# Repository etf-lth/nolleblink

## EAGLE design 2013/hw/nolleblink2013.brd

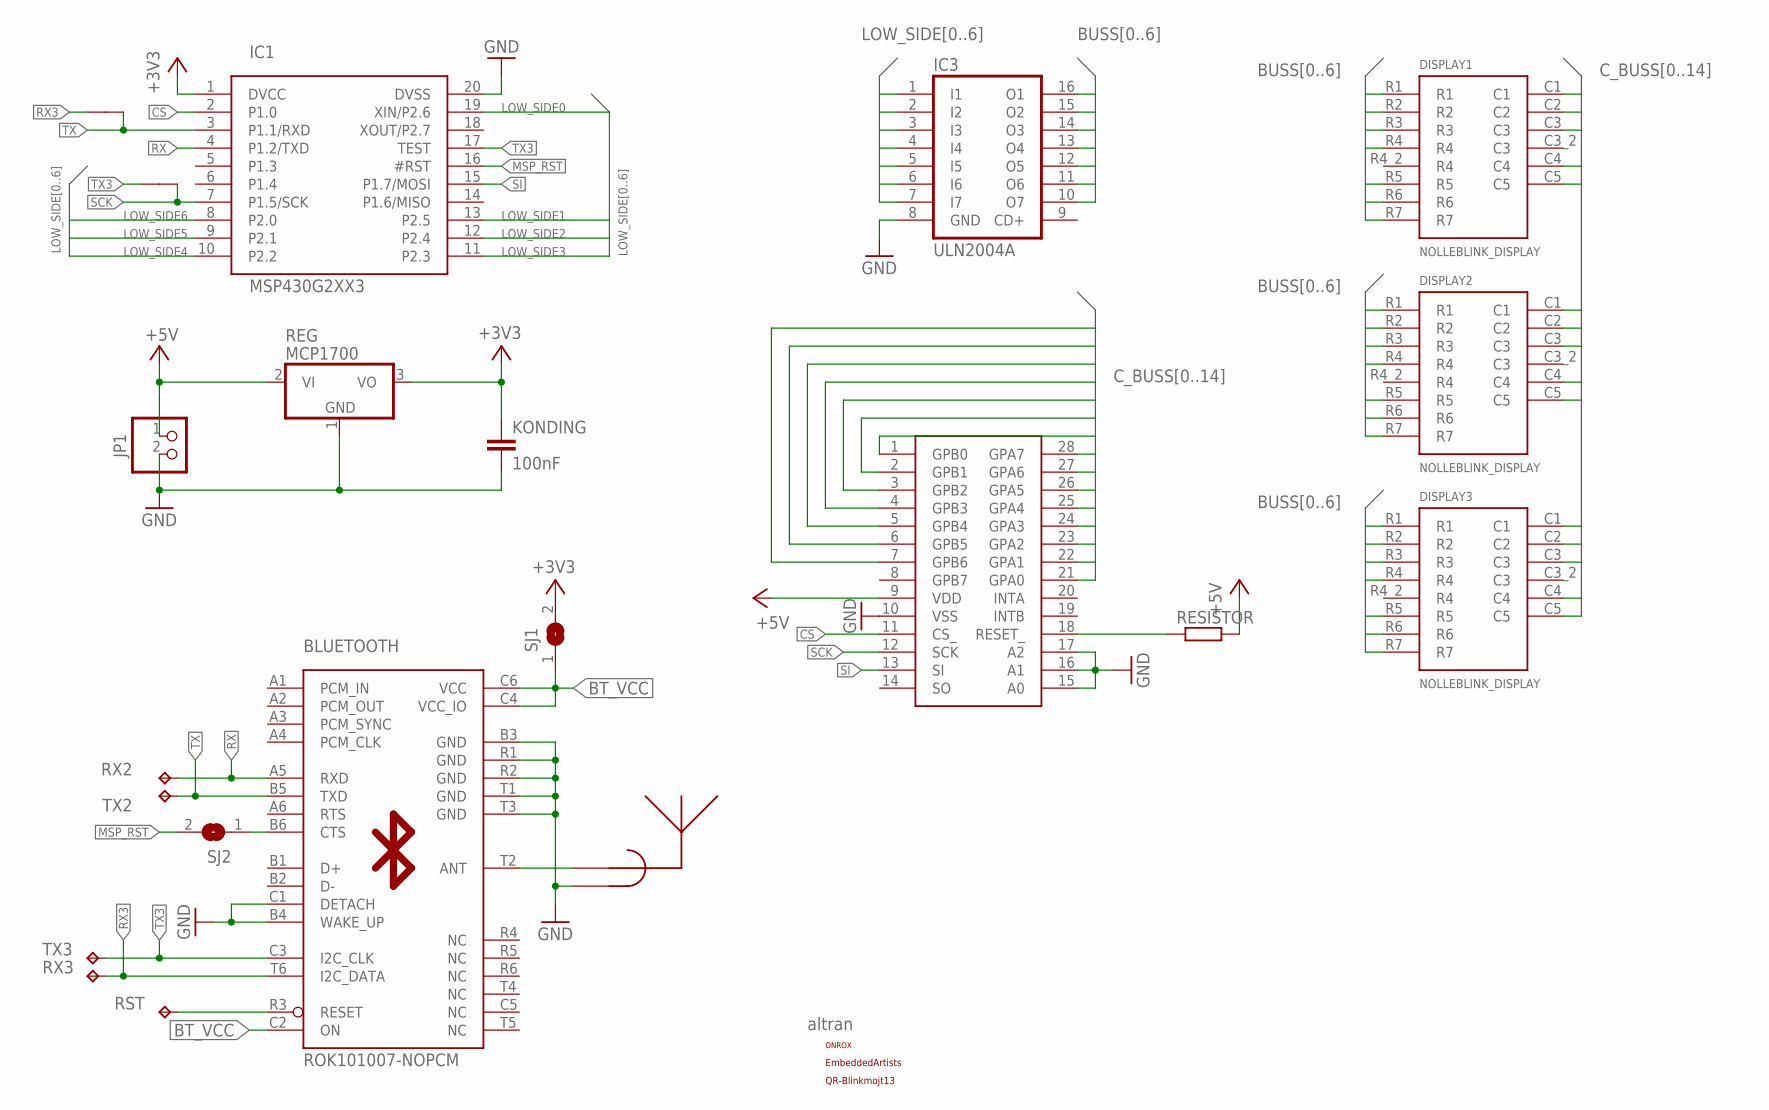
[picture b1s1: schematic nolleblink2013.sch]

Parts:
BLUETOOTH: ROK101007-NOPCM; ROK101007_NOPCM
DISPLAY1, DISPLAY2, DISPLAY3: NOLLEBLINK_DISPLAY; KINGBRIGHT_TA12-11EWA
IC1: MSP430G2XX3; N20
IC2: MCPS23S17; MCP23S17
IC3: ULN2004A; DIL16
JP1: PINHD-1X2; 1X02
KONDING: 100nF; C050-030X075
REG: MCP1700; TO92_REGULATOR
RESISTOR: R-EU_0207/10; 0207/10
RST: TPTP12SQ; TP12SQ
RX2: TPTP20SQ; TP20SQ
RX3: TPTP12SQ; TP12SQ
SJ1, SJ2: SJ
TX2: TPTP20SQ; TP20SQ
TX3: TPTP12SQ; TP12SQ
U$1: ALTRAN
U$2: ONROX
U$3: INV_F_24; INV_F_ANTENNA
U$4: EMBEDDEDARTISTS
U$5, U$6: JUNCTION
U$7: BLINKMOJT13

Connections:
+3V3: IC1.1 (DVCC), KONDING.1, REG.3 (VO), SJ1.2
+5V: IC2.9 (VDD), JP1.1, REG.2 (VI), RESISTOR.2
BT_VCC: BLUETOOTH.C2 (ON), BLUETOOTH.C4 (VCC_IO), BLUETOOTH.C6 (VCC), SJ1.1
BUSS0: DISPLAY1.R1, DISPLAY2.R1, DISPLAY3.R1, IC3.16 (O1)
BUSS1: DISPLAY1.R2, DISPLAY2.R2, DISPLAY3.R2, IC3.15 (O2)
BUSS2: DISPLAY1.R3, DISPLAY2.R3, DISPLAY3.R3, IC3.14 (O3)
BUSS3: DISPLAY1.R4, DISPLAY2.R4, DISPLAY3.R4, IC3.13 (O4)
BUSS4: DISPLAY1.R5, DISPLAY2.R5, DISPLAY3.R5, IC3.12 (O5)
BUSS5: DISPLAY1.R6, DISPLAY2.R6, DISPLAY3.R6, IC3.11 (O6)
BUSS6: DISPLAY1.R7, DISPLAY2.R7, DISPLAY3.R7, IC3.10 (O7)
CS: IC1.2 (P1.0), IC2.11 (CS_)
C_BUSS0: DISPLAY1.C1, IC2.21 (GPA0)
C_BUSS1: DISPLAY1.C2, IC2.22 (GPA1)
C_BUSS2: DISPLAY1.C3, IC2.23 (GPA2)
C_BUSS3: DISPLAY1.C4, IC2.24 (GPA3)
C_BUSS4: DISPLAY1.C5, IC2.25 (GPA4)
C_BUSS5: DISPLAY2.C1, IC2.26 (GPA5)
C_BUSS6: DISPLAY2.C2, IC2.27 (GPA6)
C_BUSS7: DISPLAY2.C3, IC2.28 (GPA7)
C_BUSS8: DISPLAY2.C4, IC2.1 (GPB0)
C_BUSS9: DISPLAY2.C5, IC2.2 (GPB1)
C_BUSS10: DISPLAY3.C1, IC2.3 (GPB2)
C_BUSS11: DISPLAY3.C2, IC2.4 (GPB3)
C_BUSS12: DISPLAY3.C3, IC2.5 (GPB4)
C_BUSS13: DISPLAY3.C4, IC2.6 (GPB5)
C_BUSS14: DISPLAY3.C5, IC2.7 (GPB6)
GND: BLUETOOTH.B3 (GND), BLUETOOTH.B4 (WAKE_UP), BLUETOOTH.C1 (DETACH), BLUETOOTH.R1 (GND), BLUETOOTH.R2 (GND), BLUETOOTH.T1 (GND), BLUETOOTH.T3 (GND), IC1.20 (DVSS), IC2.10 (VSS), IC2.15 (A0), IC2.16 (A1), IC2.17 (A2), IC3.8 (GND), JP1.2, KONDING.2, REG.1 (GND), U$3.GND
LOW_SIDE0: IC1.19 (XIN/P2.6), IC3.7 (I7)
LOW_SIDE1: IC1.13 (P2.5), IC3.6 (I6)
LOW_SIDE2: IC1.12 (P2.4), IC3.5 (I5)
LOW_SIDE3: IC1.11 (P2.3), IC3.4 (I4)
LOW_SIDE4: IC1.10 (P2.2), IC3.3 (I3)
LOW_SIDE5: IC1.9 (P2.1), IC3.2 (I2)
LOW_SIDE6: IC1.8 (P2.0), IC3.1 (I1)
MSP_RST: IC1.16 (#RST), SJ2.2
unnamed: BLUETOOTH.B6 (CTS), SJ2.1
unnamed: IC2.18 (RESET_), RESISTOR.1
unnamed: BLUETOOTH.T2 (ANT), U$3.FEED (RF)
unnamed: BLUETOOTH.R3 (RESET), RST.TP
RX: BLUETOOTH.A5 (RXD), IC1.4 (P1.2/TXD), RX2.TP
RX3: BLUETOOTH.T6 (I2C_DATA), RX3.TP, U$6.P$2
SCK: IC1.7 (P1.5/SCK), IC2.12 (SCK), U$5.P$1
SI: IC1.15 (P1.7/MOSI), IC2.13 (SI)
TX: BLUETOOTH.B5 (TXD), IC1.3 (P1.1/RXD), TX2.TP, U$6.P$1
TX3: BLUETOOTH.C3 (I2C_CLK), IC1.17 (TEST), TX3.TP, U$5.P$2

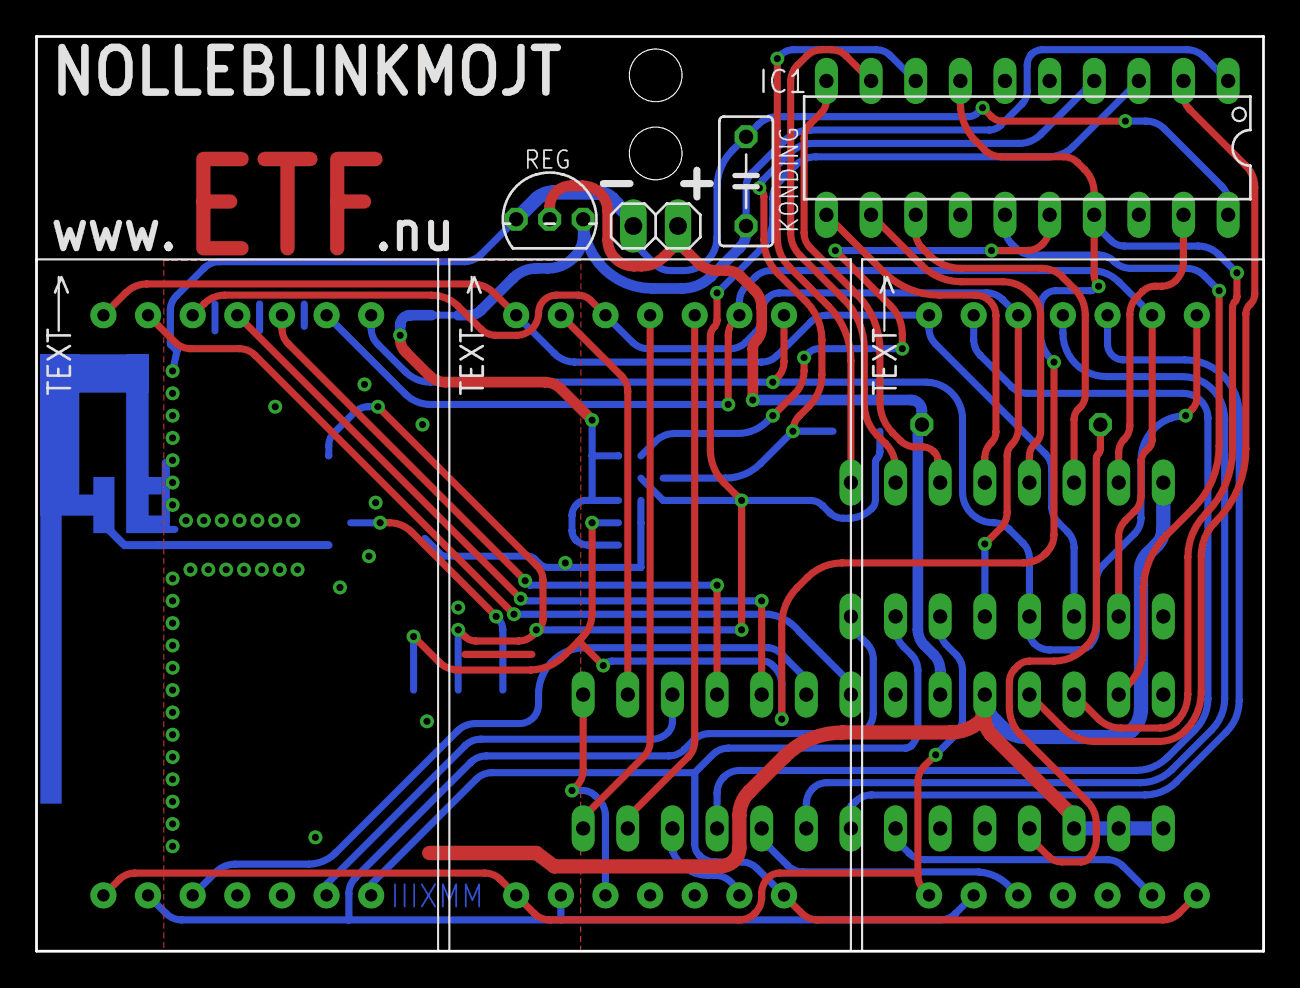
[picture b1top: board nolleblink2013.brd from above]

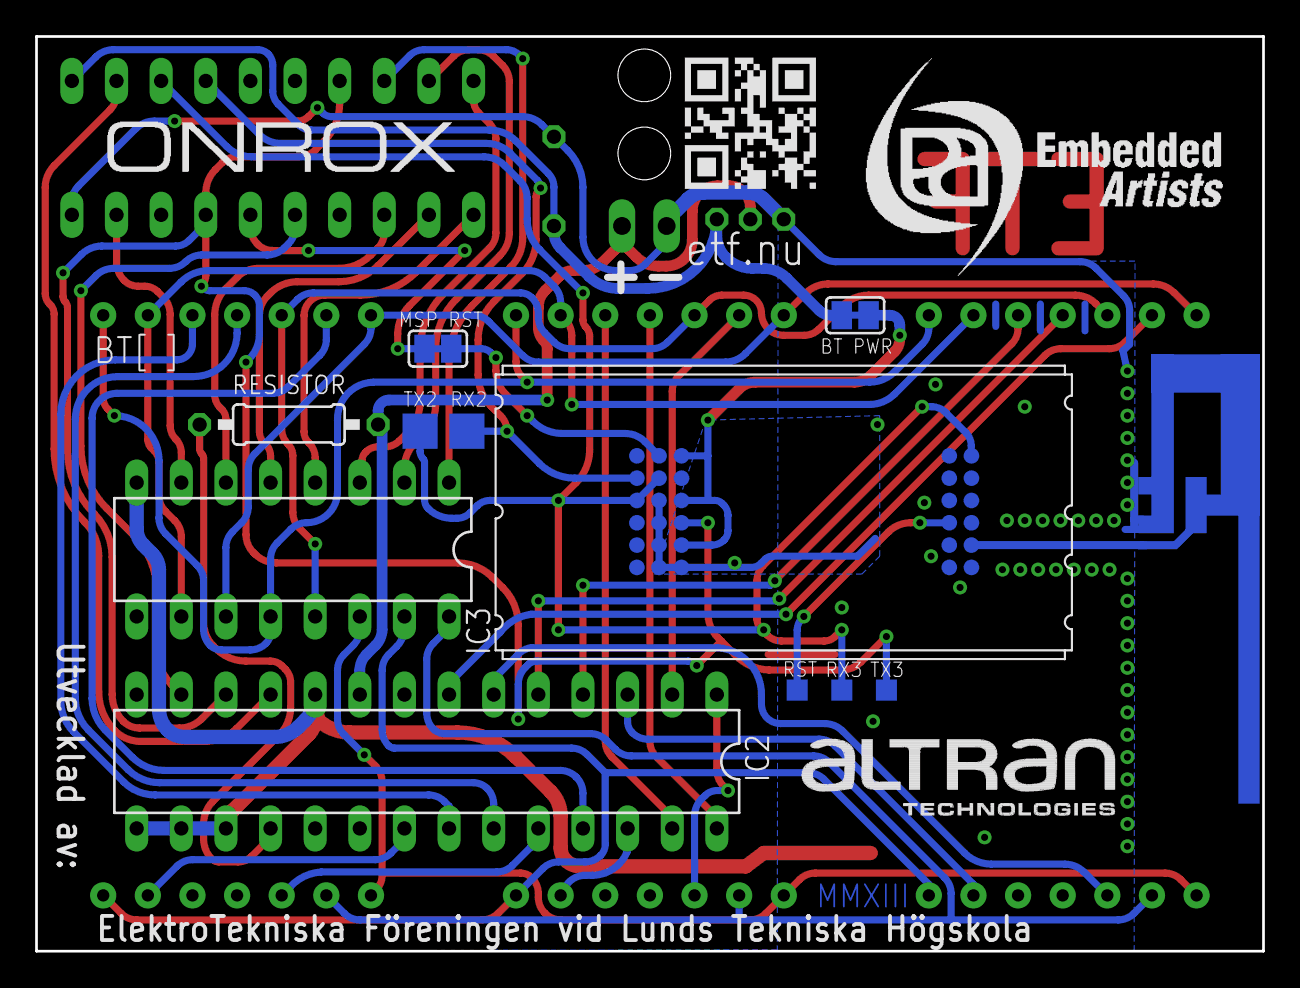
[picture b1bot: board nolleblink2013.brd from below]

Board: 2 copper layers, 69.8 x 52.1 mm, 25 parts (16 on the bottom side), 45 nets.

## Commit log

2011-08-23 init
2011-08-23 imported 2010
2011-08-24 added 2011
2011-12-21 nollor
2012-03-07 2009
2012-06-17 unicode fix!
2012-07-17 2010 hw
2012-07-17 2009 hw
2012-07-17 hw initial
2012-07-26 2012 hw
2012-07-26 2012 hw final?
2012-08-02 2012 fw init
2012-08-02 indent
2012-08-14 added notes to 2012 hw
2012-08-15 softuart rx working
2012-08-15 2012 fw wip
2012-08-15 2012 fw softu wip
2012-08-17 2012 fw fifo
2012-09-11 2012 fw final
2012-09-11 2012 pyblink
2012-10-01 pogo board for 2012 hw
2013-07-16 2013 hw done?
2013-07-18 import 2013 fw
2013-08-23 cleanup
2013-08-23 firmware wip
2013-08-25 deferred uart handling with fifo
2013-08-25 reduced led duty cycle
2013-08-26 nolle13: sbwconf
2013-08-26 nolle13: firmware, done?
2018-10-21 added 2013 btflash scripts
